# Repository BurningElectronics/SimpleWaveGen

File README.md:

# SimpleWaveGen
A simple waveform generator using Arduino nano and a few more components

The components used are:

1. Arduino nano
2. SSD1306 32x128 OLED display
3. AD9833 waveform generator module
4. 2x Screw terminal (2P 5.0mm)
5. RL207 diode, you can use anyone you want, as long as it fits
6. SS12F44G4 Switch
7. 50V 100uF Capacitor (D8.0mm, P3.50mm), symbolic value
8. 3x 2-Pin Pushbuttons
9. Some female headers
10. 8x 10k 1/4W resistors, you can use any reasonable value for pull-up/down purposes

<br/>
<br/>
<br/>

How does it work?

The arduino nano sends the waveform type and frequency via SPI to the AD9833, that generates the requested waveform.

While doing this, the OLED display (SSD1306) is updated by the arduino via I2C, with dsplayed frequency, waveform type and digit position.

To set the frequency an encoder it's used.

To navigate between digits two pushbuttons, LEFT (<-) and RIGHT (->), are used.

To change Waveform type a third pushbutton (MODE) it's used.

To reset the digit press the encoder button.

Want this PCB manufactured?
Check www.pcbway.com
You can directly upload the file in the gerber folder and customize as you wish!

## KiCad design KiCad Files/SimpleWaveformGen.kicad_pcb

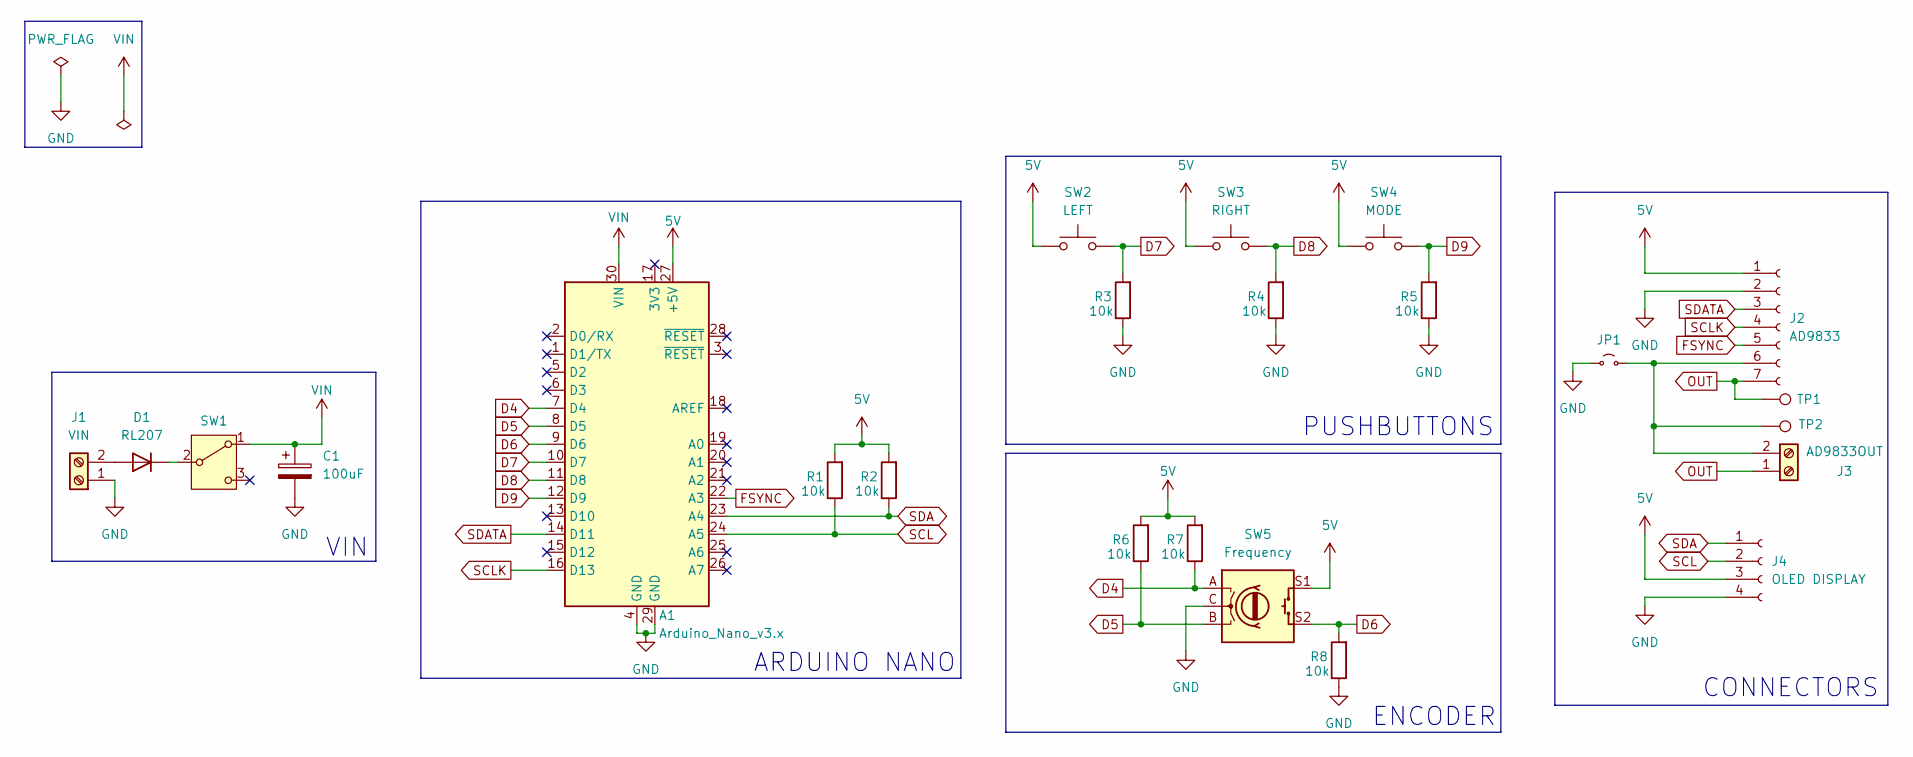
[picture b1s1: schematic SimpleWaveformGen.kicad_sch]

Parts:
A1: Arduino_Nano_v3.x; Arduino_Nano
C1: 100uF; CP_Radial_D8.0mm_P3.50mm
D1: RL207; D_DO-15_P12.70mm_Horizontal
J1: VIN; ScrewTerminal-2P
J2: AD9833; PinSocket_1x07_P2.54mm_Vertical
J3: AD9833OUT; ScrewTerminal-2P
J4: OLED DISPLAY; PinSocket_1x04_P2.54mm_Vertical
JP1: Jumper_2_Small_Open; SolderJumper-2_P1.3mm_Open_RoundedPad1.0x1.5mm
R1, R2, R3, R4, R5, R6, R7, R8: 10k; R_Axial_DIN0207_L6.3mm_D2.5mm_P10.16mm_Horizontal
SW1: SW_SPDT; Switxh SPDT - SS12F44G4
SW2: LEFT; Pushbutton - DIP-2
SW3: RIGHT; Pushbutton - DIP-2
SW4: MODE; Pushbutton - DIP-2
SW5: Frequency; RotaryEncoder_Alps_EC11E-Switch_Vertical_H20mm
TP1, TP2: TestPoint; PinHeader_1x01_P2.54mm_Vertical

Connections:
5V: A1.27 (+5V), J2.1, J4.3, R1.2, R2.2, R6.2, R7.2, SW2.1, SW3.1, SW4.1, SW5.S1
D4: A1.7 (D4), R7.1, SW5.A
D5: A1.8 (D5), R6.1, SW5.B
D6: A1.9 (D6), R8.2, SW5.S2
D7: A1.10 (D7), R3.2, SW2.2
D8: A1.11 (D8), R4.2, SW3.2
D9: A1.12 (D9), R5.2, SW4.2
FSYNC: A1.22 (A3), J2.5
GND: A1.4 (GND), A1.29 (GND), C1.2, J1.1, J2.2, J4.4, JP1.1 (A), R3.1, R4.1, R5.1, R8.1, SW5.C
unnamed: D1.2 (A), J1.2
unnamed: D1.1 (K), SW1.2 (B)
unnamed: J2.6, J3.2, JP1.2 (B), TP2.1
OUT: J2.7, J3.1, TP1.1
SCL: A1.24 (A5), J4.2, R1.1
SCLK: A1.16 (D13), J2.4
SDA: A1.23 (A4), J4.1, R2.1
SDATA: A1.14 (D11), J2.3
VIN: A1.30 (VIN), C1.1, SW1.1 (A)

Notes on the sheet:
CONNECTORS
VIN
ENCODER
ARDUINO NANO
PUSHBUTTONS

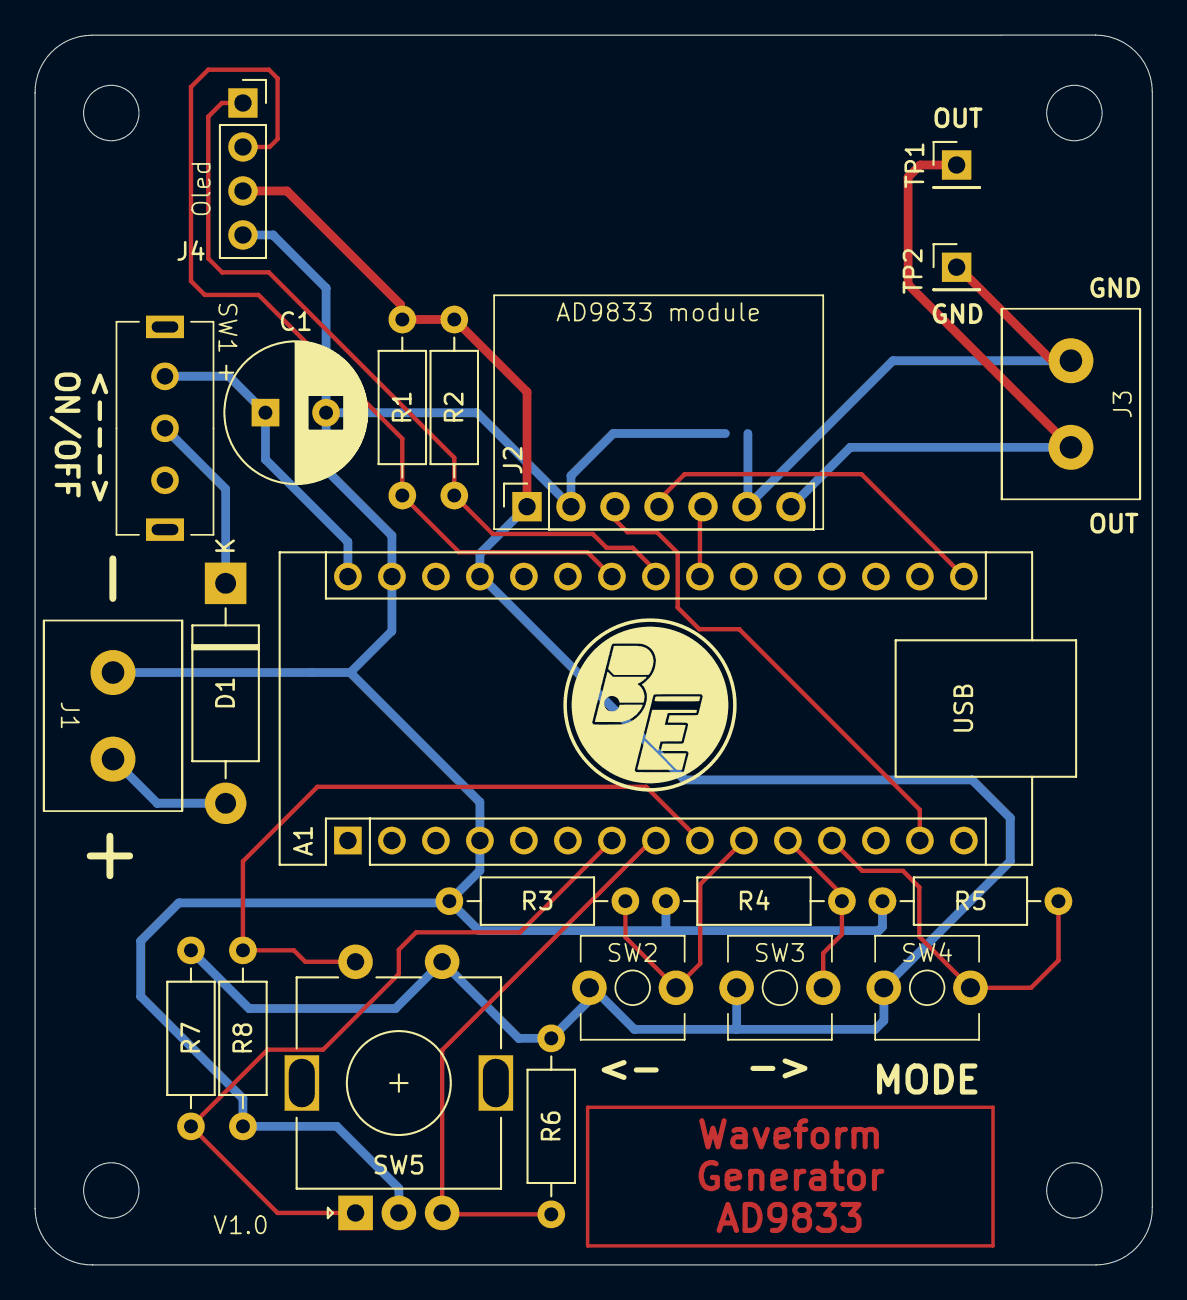
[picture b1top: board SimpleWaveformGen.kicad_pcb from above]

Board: 2 copper layers, 64.5 x 71.0 mm, 23 parts (1 on the bottom side), 18 nets.

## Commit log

2025-01-17 KiCad Files
2025-01-17 Custom Footprint for Switch
2025-01-17 Custom footprint for Screw Terminal
2025-01-17 Arduino file
2025-01-17 Gerbers for PCBWay
